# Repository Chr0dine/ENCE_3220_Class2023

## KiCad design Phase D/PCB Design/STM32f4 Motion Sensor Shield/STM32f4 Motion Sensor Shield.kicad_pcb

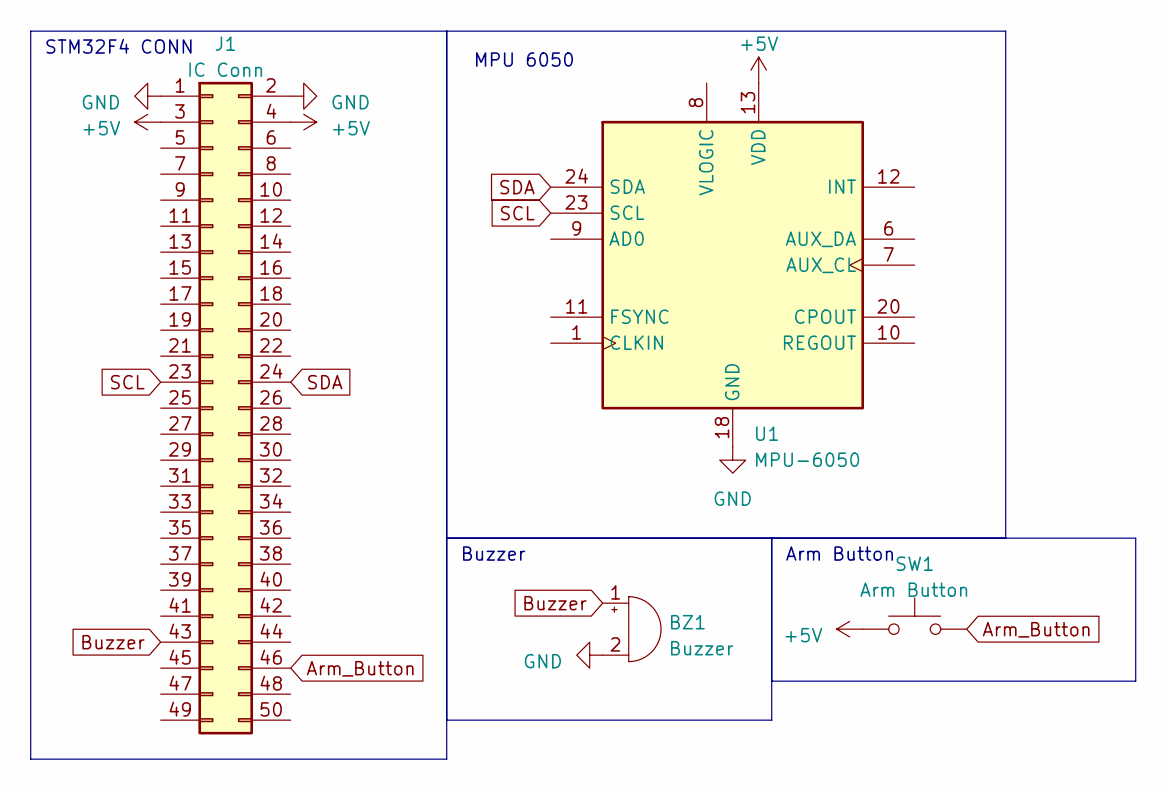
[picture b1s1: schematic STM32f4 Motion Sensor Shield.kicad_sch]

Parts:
BZ1: Buzzer; Buzzer_12x9.5RM7.6
J1: IC Conn; PinSocket_2x25_P2.54mm_Vertical
SW1: Arm Button; SW_SPST_B3U-1000P
U1: MPU-6050; InvenSense_QFN-24_4x4mm_P0.5mm

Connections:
+5V: J1.3, J1.4, SW1.1, U1.13 (VDD)
Arm_Button: J1.46, SW1.2
Buzzer: BZ1.1 (-), J1.43
GND: BZ1.2 (+), J1.1, J1.2, U1.18 (GND)
SCL: J1.23, U1.23 (SCL)
SDA: J1.24, U1.24 (SDA)

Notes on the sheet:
STM32F4 CONN
Arm Button
MPU 6050
Buzzer

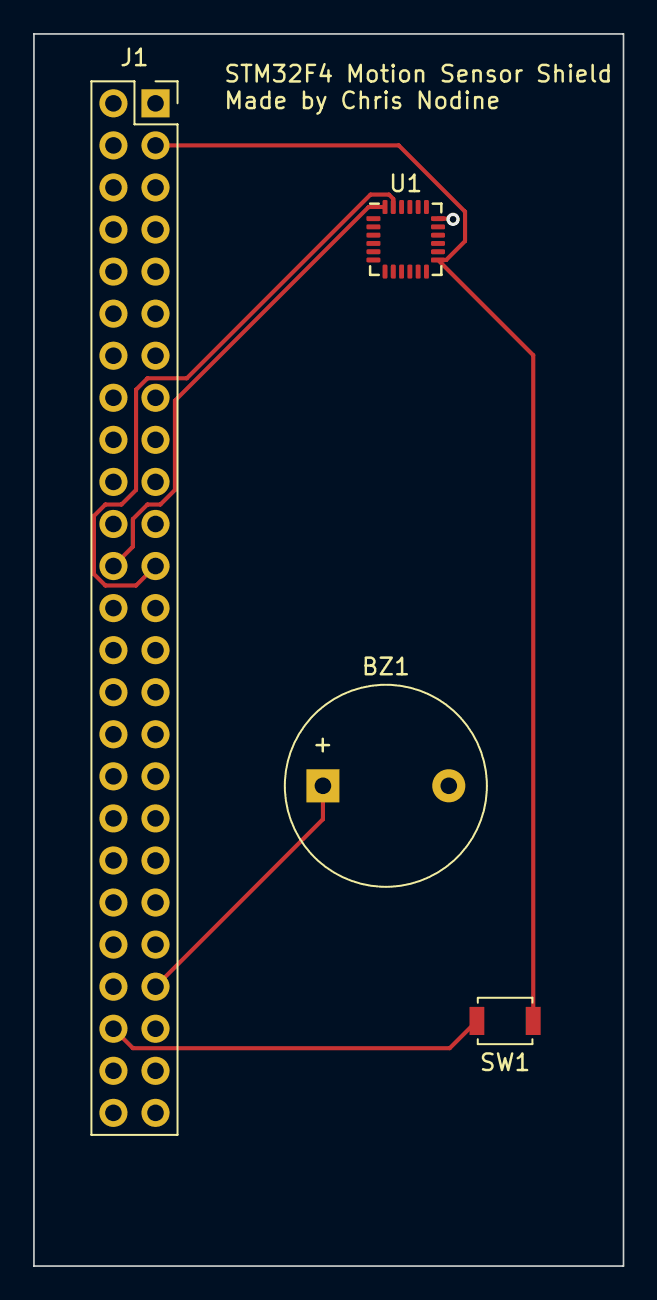
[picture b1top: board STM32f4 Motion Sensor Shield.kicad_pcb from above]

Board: 2 copper layers, 35.6 x 74.4 mm, 4 parts (0 on the bottom side), 6 nets.

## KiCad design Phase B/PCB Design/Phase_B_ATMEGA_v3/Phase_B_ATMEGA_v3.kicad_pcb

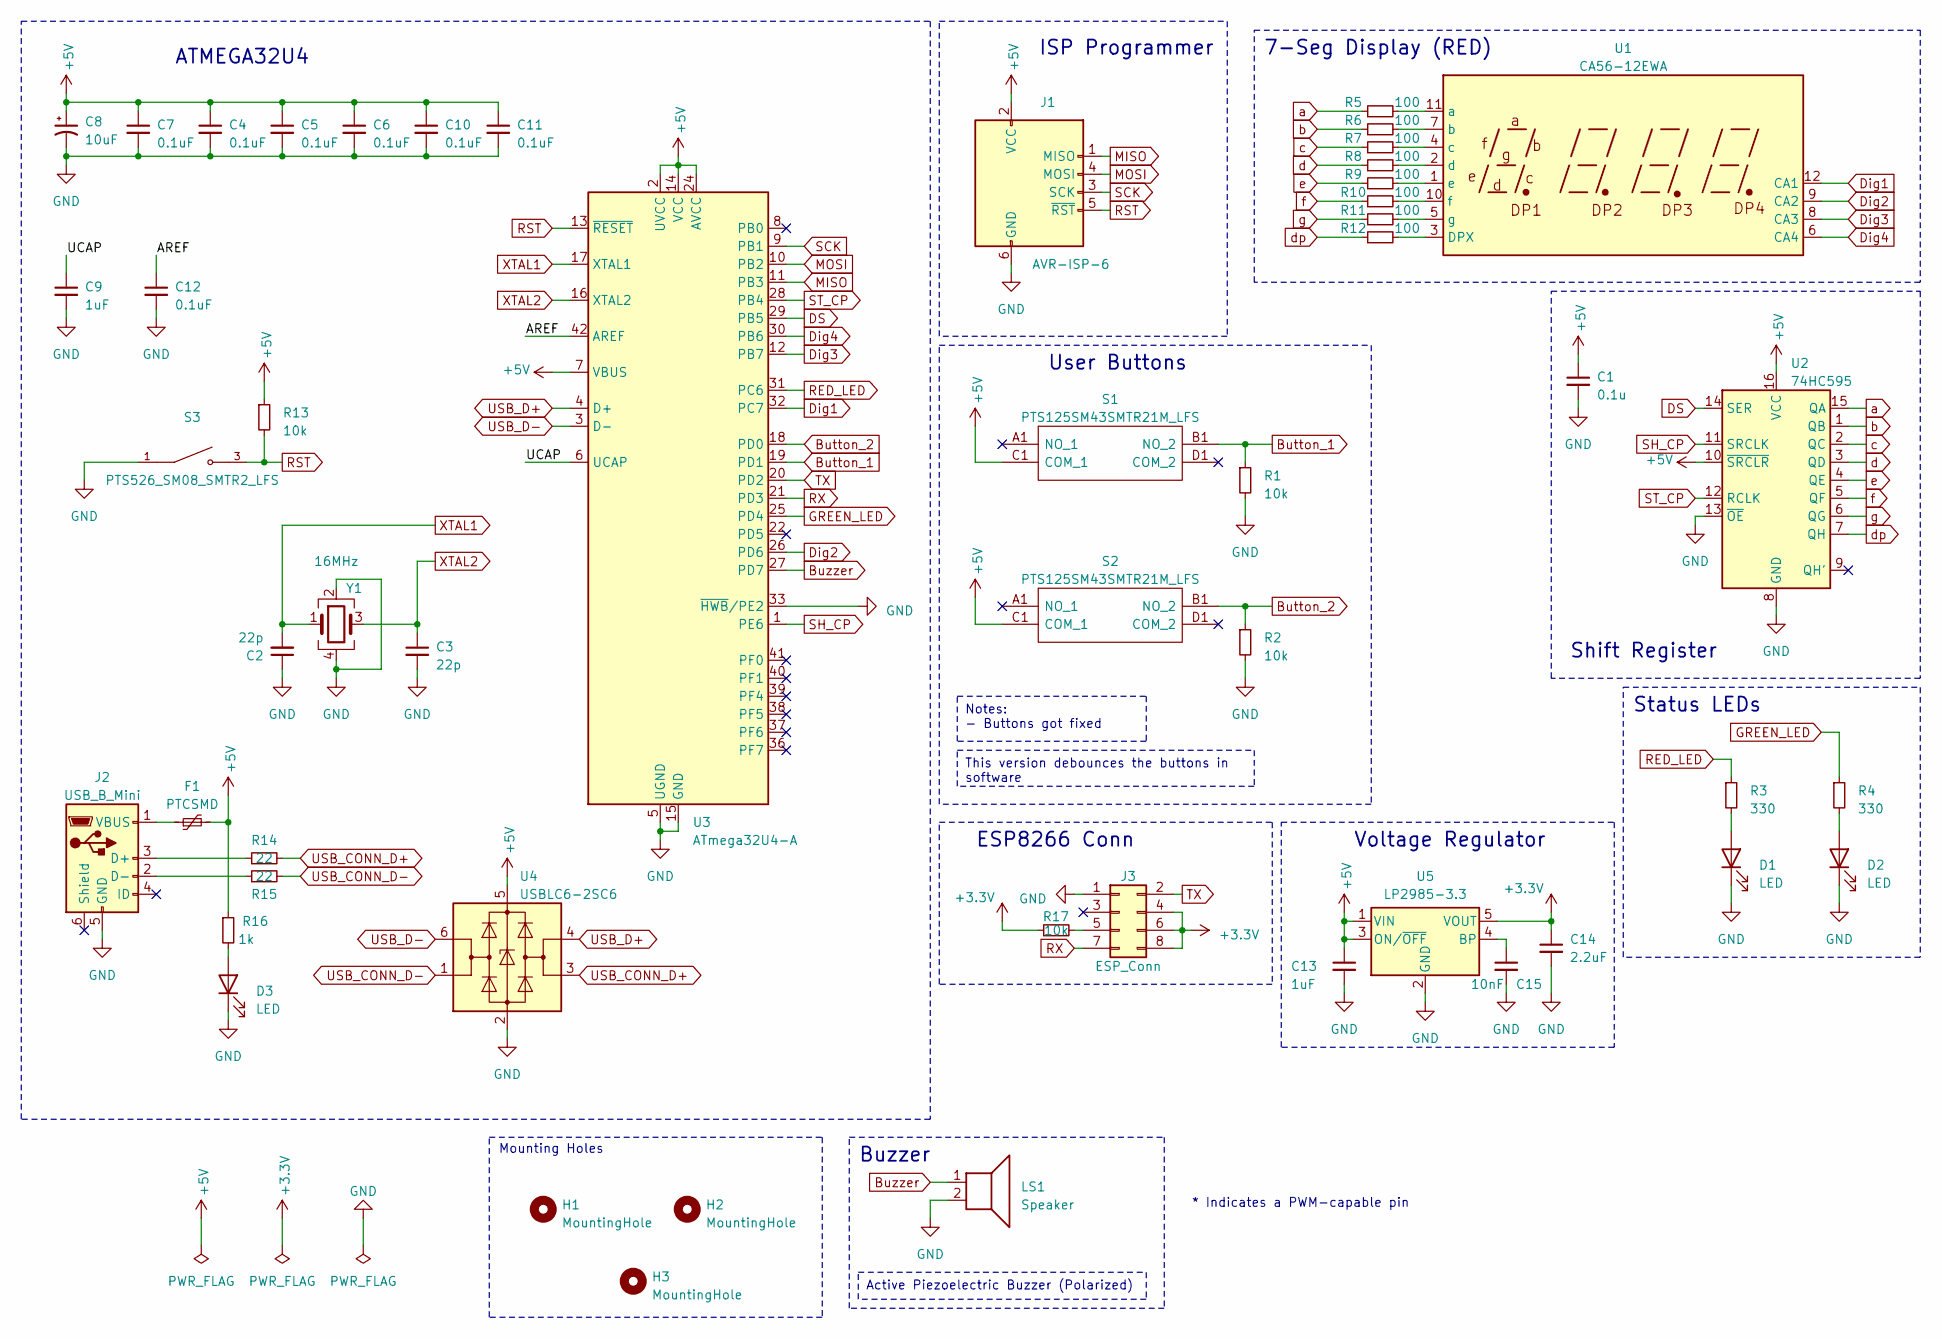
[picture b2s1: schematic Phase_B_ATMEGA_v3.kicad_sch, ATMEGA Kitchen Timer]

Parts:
C1: 0.1u; C_0603_1608Metric
C2, C3: 22p; C_0603_1608Metric
C4, C5, C6, C7, C10, C11, C12: 0.1uF; C_0603_1608Metric
C8: 10uF; C_0805_2012Metric
C9, C13: 1uF; C_0603_1608Metric
C14: 2.2uF; C_0603_1608Metric
C15: 10nF; C_0603_1608Metric
D1, D2, D3: LED; LED_0805_2012Metric
F1: PTCSMD; Fuse_1812_4532Metric
H1, H2, H3: MountingHole; MountingHole_2.2mm_M2
J1: AVR-ISP-6; PinSocket_2x03_P2.54mm_Vertical
J2: USB_B_Mini; USB_Mini-B_Lumberg_2486_01_Horizontal
J3: ESP_Conn; PinSocket_2x04_P2.54mm_Vertical
LS1: Speaker; Buzzer_12x9.5RM7.6
R1, R2: 10k; R_0805_2012Metric
R3, R4: 330; R_0805_2012Metric
R5, R6, R7, R8, R9, R10, R11, R12: 100; R_0805_2012Metric
R13, R17: 10k; R_0603_1608Metric
R14, R15: 22; R_0603_1608Metric
R16: 1k; R_0603_1608Metric
S1, S2: PTS125SM43SMTR21M_LFS; PTS125_SMD_Button; Manufacturer_Part_Number PTS125SM43SMTR21M LFS; Mouser Part Number 611-PTS125S43SMTRLFS
S3: PTS526_SM08_SMTR2_LFS; PTS526_SMD_Button; PARTREV 20 mar 19
U1: CA56-12EWA
U2: 74HC595; TSSOP-16_4.4x5mm_P0.65mm
U3: ATmega32U4-A; TQFP-44_10x10mm_P0.8mm
U4: USBLC6-2SC6; SOT-23-6
U5: LP2985-3.3; SOT-23-5
Y1: 16MHz; Crystal_SMD_Abracon_ABM8G-4Pin_3.2x2.5mm

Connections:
+3.3V: C14.1, J3.4, J3.6, J3.8, R17.1, U5.5 (VOUT)
+5V: C1.1, C4.1, C5.1, C6.1, C7.1, C8.1, C10.1, C11.1, C13.1, F1.2, J1.2 (VCC), R13.1, R16.1, S1.C1 (COM_1), S2.C1 (COM_1), U2.10 (~SRCLR), U2.16 (VCC), U3.2 (UVCC), U3.7 (VBUS), U3.14 (VCC), U3.24 (AVCC), U3.34 (VCC), U3.44 (AVCC), U4.5 (VBUS), U5.1 (VIN), U5.3 (ON/~OFF)
/AREF: C12.1, U3.42 (AREF)
/UCAP: C9.1, U3.6 (UCAP)
Button_1: R1.1, S1.B1 (NO_2), U3.19 (PD1)
Button_2: R2.1, S2.B1 (NO_2), U3.18 (PD0)
Buzzer: LS1.1, U3.27 (PD7)
DS: U2.14 (SER), U3.29 (PB5)
Dig1: U1.12 (CA1), U3.32 (PC7)
Dig2: U1.9 (CA2), U3.26 (PD6)
Dig3: U1.8 (CA3), U3.12 (PB7)
Dig4: U1.6 (CA4), U3.30 (PB6)
GND: C1.2, C2.1, C3.2, C4.2, C5.2, C6.2, C7.2, C8.2, C9.2, C10.2, C11.2, C12.2, C13.2, C14.2, C15.2, D1.1 (K), D2.1 (K), D3.1 (K), J1.6 (GND), J2.5 (GND), J3.1, LS1.2, R1.2, R2.2, S3.1, U2.8 (GND), U2.13 (~OE), U3.5 (UGND), U3.15 (GND), U3.23 (GND), U3.33 (~HWB/PE2), U3.35 (GND), U3.43 (GND), U4.2 (GND), U5.2 (GND), Y1.2, Y1.4
GREEN_LED: R4.1, U3.25 (PD4)
MISO: J1.1 (MISO), U3.11 (PB3)
MOSI: J1.4 (MOSI), U3.10 (PB2)
unnamed: D1.2 (A), R3.2
unnamed: D2.2 (A), R4.2
unnamed: D3.2 (A), R16.2
unnamed: J2.3 (D+), R14.1
unnamed: J2.2 (D-), R15.1
unnamed: F1.1, J2.1 (VBUS)
unnamed: J3.5, R17.2
unnamed: R12.2, U1.3 (DPX)
unnamed: R5.2, U1.11 (a)
unnamed: R6.2, U1.7 (b)
unnamed: R7.2, U1.4 (c)
unnamed: R8.2, U1.2 (d)
unnamed: R9.2, U1.1 (e)
unnamed: R10.2, U1.10 (f)
unnamed: R11.2, U1.5 (g)
unnamed: C15.1, U5.4 (BP)
RED_LED: R3.1, U3.31 (PC6)
RST: J1.5 (~RST), R13.2, S3.3, U3.13 (~RESET)
RX: J3.7, U3.21 (PD3)
SCK: J1.3 (SCK), U3.9 (PB1)
SH_CP: U2.11 (SRCLK), U3.1 (PE6)
ST_CP: U2.12 (RCLK), U3.28 (PB4)
TX: J3.2, U3.20 (PD2)
USB_CONN_D+: R14.2, U4.3 (I/O2)
USB_CONN_D-: R15.2, U4.1 (I/O1)
USB_D+: U3.4 (D+), U4.4 (I/O2)
USB_D-: U3.3 (D-), U4.6 (I/O1)
XTAL1: C2.2, U3.17 (XTAL1), Y1.1
XTAL2: C3.1, U3.16 (XTAL2), Y1.3
a: R5.1, U2.15 (QA)
b: R6.1, U2.1 (QB)
c: R7.1, U2.2 (QC)
d: R8.1, U2.3 (QD)
dp: R12.1, U2.7 (QH)
e: R9.1, U2.4 (QE)
f: R10.1, U2.5 (QF)
g: R11.1, U2.6 (QG)

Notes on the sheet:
Notes: - Buttons got fixed
Active Piezoelectric Buzzer (Polarized)
This version debounces the buttons in software
Shift Register
Mounting Holes
Voltage Regulator
Status LEDs
ATMEGA32U4
User Buttons
Buzzer
* Indicates a PWM-capable pin
7-Seg Display (RED)
ISP Programmer
ESP8266 Conn

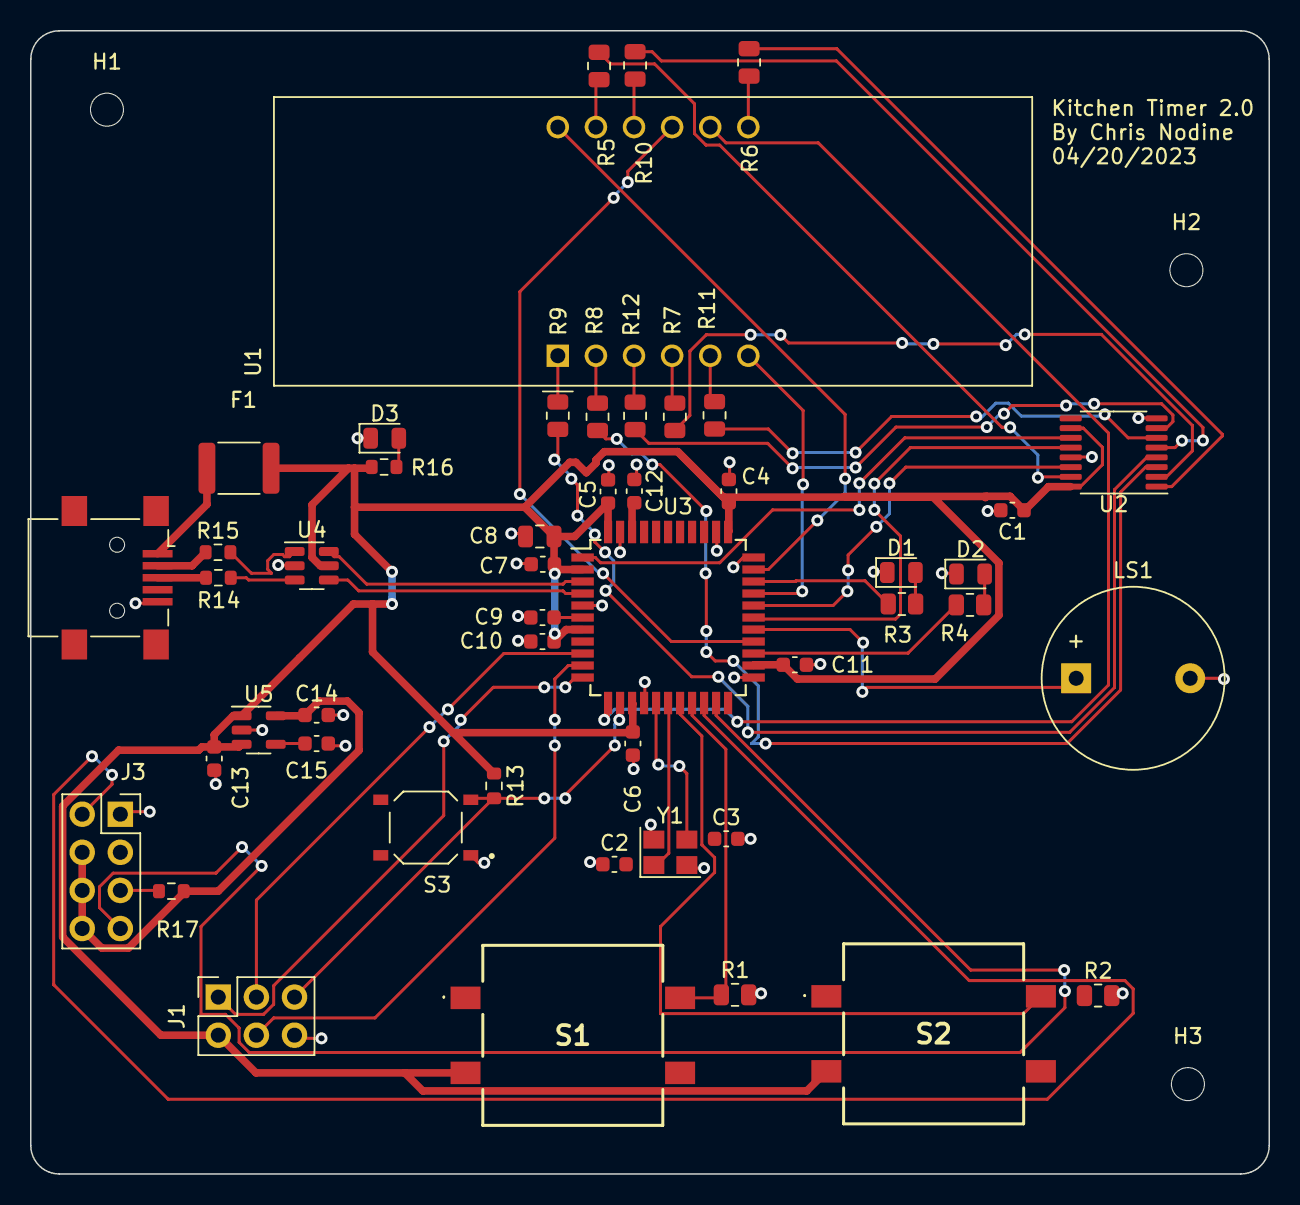
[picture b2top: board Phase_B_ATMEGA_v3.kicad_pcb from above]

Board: 2 copper layers, 82.5 x 76.2 mm, 52 parts (0 on the bottom side), 53 nets.

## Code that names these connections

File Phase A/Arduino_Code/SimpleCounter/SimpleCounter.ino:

#include <Arduino_FreeRTOS.h>

#define BUTTON_1  2
#define BUTTON_2  3
#define GREEN_LED 4
#define RED_LED   5
#define BUZZER    6

#define DATA      9
#define LATCH     8
#define CLOCK     7

#define DIGIT_4   10
#define DIGIT_3   11
#define DIGIT_2   12
#define DIGIT_1   13

volatile int gTime=0;
const int DEBOUNCE_DELAY_MS = 50;
bool lastButtonState = HIGH;
volatile unsigned char firstDigit =0;
volatile unsigned char secondDigit =0;
volatile unsigned char thirdDigit =0;
volatile unsigned char fourthDigit =0;
volatile int count = 387;
static unsigned char hexZero = 0x3f;
static unsigned char hexOne = 0x06;
static unsigned char hexTwo = 0x5b;
static unsigned char hexThree = 0x4f;
static unsigned char hexFour = 0x66;
static unsigned char hexFive = 0x6d;
static unsigned char hexSix = 0x7d;
static unsigned char hexSeven = 0x07;
static unsigned char hexEight = 0x7f;
static unsigned char hexNine = 0x6f;
volatile bool buttonTwoFlag = false;

void setup() {
  Serial.begin(9600);
  // LEDs Pins
  pinMode(RED_LED, OUTPUT);
  pinMode(GREEN_LED, OUTPUT);
  // Button Pins
  pinMode(BUTTON_1, INPUT_PULLUP);
  attachInterrupt(digitalPinToInterrupt(BUTTON_1), Button_1_ISR, RISING);
  pinMode(BUTTON_2, INPUT_PULLUP);
  attachInterrupt(digitalPinToInterrupt(BUTTON_2), Button_2_ISR, RISING);

  // Buzer Pins
  pinMode(BUZZER, OUTPUT);

  // 7-Seg Display
  pinMode(DIGIT_1, OUTPUT);
  pinMode(DIGIT_2, OUTPUT);
  pinMode(DIGIT_3, OUTPUT);
  pinMode(DIGIT_4, OUTPUT);

  // Shift Register Pins
  pinMode(LATCH, OUTPUT);
  pinMode(CLOCK, OUTPUT);
  pinMode(DATA, OUTPUT);

  disp_off();
  // Timer initialization
  noInterrupts();           // disable all interrupts
  //timer 1 initialization
  TCCR1B = 0;
  TCNT1  = 0;
  OCR1A = 62500;            // compare match register 16MHz/256
  TCCR1B |= (1 << WGM12);   // CTC mode
  TCCR1B |= (1 << CS12);    // 256 prescaler 
  TIMSK1 |= (1 << OCIE1A);  // enable timer compare interrupt

//timer 2 initialization
  TCCR2A = 0;
  TCCR2B = 0;
  TCNT2  = 0;
  OCR2A = 62500;            // compare match register 16MHz/256
  TCCR2B |= (1 << WGM12);   // CTC mode
  TCCR2B |= (1 << CS22) | (1 <<CS20); //1024 prescaler
  TIMSK2 |= (1 << OCIE2A);  // enable timer compare interrupt
  interrupts(); 
}

void disp_off(){
  digitalWrite(DIGIT_1,HIGH);
  digitalWrite(DIGIT_2,HIGH);
  digitalWrite(DIGIT_3,HIGH);
  digitalWrite(DIGIT_4,HIGH);  
}

unsigned char numToHEX(int num){
 unsigned char outputNum = 0;
if(num==0){
    outputNum = hexZero;
  }else if(num==1){
    outputNum = hexOne;
  }else if(num==2){
    outputNum = hexTwo;
  }else if(num==3){
    outputNum = hexThree;
  }else if(num==4){
    outputNum = hexFour;
  }else if(num==5){
    outputNum = hexFive;
  }else if(num==6){
    outputNum = hexSix;
  }else if(num==7){
    outputNum = hexSeven;
  }else if(num==8){
    outputNum = hexEight;
  }else if(num==9){
    outputNum = hexNine;
  }
  return outputNum;
}

void Display(unsigned char num){
    digitalWrite(LATCH, LOW);
  shiftOut(DATA, CLOCK, MSBFIRST, num);
  digitalWrite(LATCH, HIGH);
 
}

int countToTime(int count){
  int minutes = 100 * int((count/60)%60);
  int seconds = int(count%60);
  return minutes + seconds;
}

void Button_1_ISR()
{
  unsigned int buttonState = 0;  // variable for reading the pushbutton status
    
  buttonState = digitalRead(BUTTON_1);
  if(buttonState && !buttonTwoFlag){
     count++;
  }
}

void Button_2_ISR()
{ 
  unsigned int buttonState = 0;  // variable for reading the pushbutton status
  
  buttonState = digitalRead(BUTTON_2);
  if(buttonState){
    buttonTwoFlag=true;
    digitalWrite(RED_LED,LOW);
  }else{
  buttonTwoFlag = false;   
  digitalWrite(RED_LED,HIGH);
  }
    digitalWrite(GREEN_LED, HIGH); 
  
}

ISR(TIMER1_COMPA_vect)          // timer compare interrupt service routine
{
  if(buttonTwoFlag && count>0){
  count--;
  }
  
//  Serial.println(buttonTwoFlag);  
}

ISR(TIMER2_COMPA_vect)          // timer compare interrupt service routine
{
    
  gTime = countToTime(count);
  if(count==0){
    digitalWrite(BUZZER,HIGH);
    digitalWrite(RED_LED,HIGH);
    digitalWrite(GREEN_LED,LOW);    
    digitalWrite(BUZZER,LOW); 
  }else{
  firstDigit = (int)(gTime%10);
  Display(numToHEX(firstDigit));
  digitalWrite(DIGIT_4,LOW);
  disp_off();
  secondDigit = (int)(gTime/10)%10;
  Display(numToHEX(secondDigit));
  digitalWrite(DIGIT_3,LOW);
  disp_off();
  thirdDigit = (int)((gTime/100)%10);
  Display(numToHEX(thirdDigit)| (1<<7));
  digitalWrite(DIGIT_2,LOW);
  disp_off();
  fourthDigit = (int)((gTime/1000)%10);
  Display(numToHEX(fourthDigit));
  digitalWrite(DIGIT_1,LOW);
  disp_off();
  }
}

void loop() {
  // IDLE
}

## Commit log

2023-04-11 Updating Repo file structure. Adding PCB Design and Arduino Code
2023-04-12 Added Notes
2023-04-16 Starting to implement PCB and Enclosure 1.0
2023-04-18 Enclosure Updates
2023-04-20 PCB Final Design as well as plot, gerber, and BOM updates
2023-04-20 more PCB updates
2023-04-22 3d model updates for buttons
2023-04-27 File Structure Updates and Enclosure
2023-04-27 Working Wifi Module Test Code
2023-05-02 Code with timer and wifi module v1
2023-05-03 Structural Updates and Report
2023-05-31 Phase C and D
